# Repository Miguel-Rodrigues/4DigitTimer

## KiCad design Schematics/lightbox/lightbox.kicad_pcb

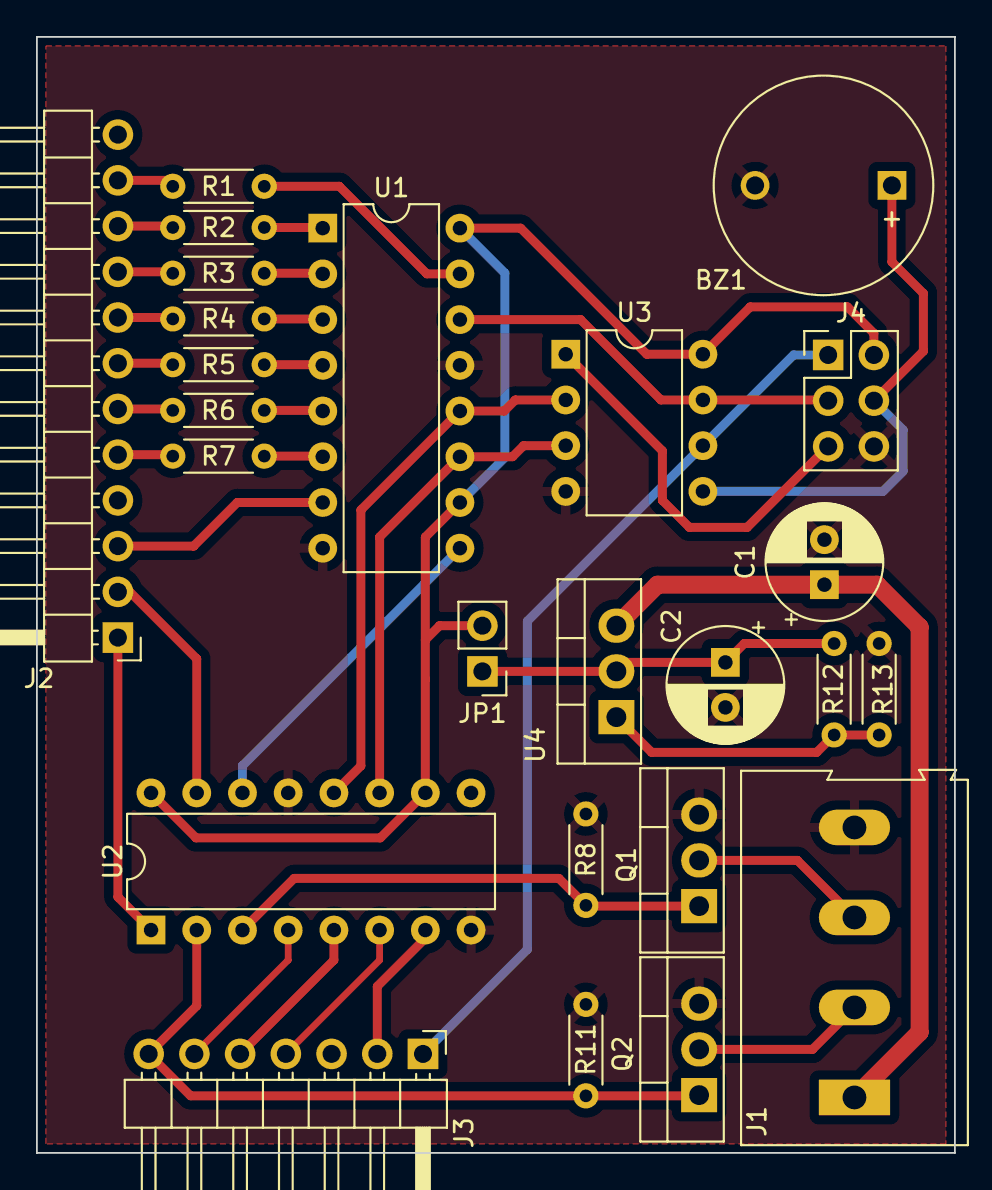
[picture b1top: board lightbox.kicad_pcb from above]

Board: 2 copper layers, 51.0 x 62.0 mm, 25 parts (0 on the bottom side), 37 nets.

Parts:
BZ1: Buzzer; MagneticBuzzer_ProSignal_ABI-010-RC
C1: 100nF; CP_Radial_D6.3mm_P2.50mm
C2: 1µF; CP_Radial_D6.3mm_P2.50mm
J1: Screw_Terminal_01x04; TerminalBlock_Altech_AK300-4_P5.00mm
J2: Conn_01x11_Pin; PinHeader_1x12_P2.54mm_Horizontal
J3: Conn_01x07_Pin; PinHeader_1x07_P2.54mm_Horizontal
J4: Conn_02x03_Odd_Even; PinHeader_2x03_P2.54mm_Vertical
JP1: Jumper_2_Bridged; PinHeader_1x02_P2.54mm_Vertical
Q1, Q2: IRF530; TO-220-3_Vertical
R1, R2, R3, R4, R5, R6, R7: 470R; R_Axial_DIN0204_L3.6mm_D1.6mm_P5.08mm_Horizontal
R8, R11: 10K; R_Axial_DIN0204_L3.6mm_D1.6mm_P5.08mm_Horizontal
R12: 100R; R_Axial_DIN0204_L3.6mm_D1.6mm_P5.08mm_Horizontal
R13: 220R; R_Axial_DIN0204_L3.6mm_D1.6mm_P5.08mm_Horizontal
U1: 74AHCT595; DIP-16_W7.62mm
U2: 74HC595; DIP-16_W7.62mm
U3: ATtiny85-20P; DIP-8_W7.62mm
U4: LM317_TO-220; TO-220-3_Vertical

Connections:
+12V: C1.1, J1.1, U4.3 (VI)
/A: J2.11, R1.2
/B: J2.10, R2.2
/Buzzer: BZ1.1 (-), J4.4, U3.5 (AREF/PB0)
/C: J2.9, R3.2
/Clk: U1.11 (SRCLK), U2.11 (SRCLK), U3.3 (XTAL2/PB4)
/D: J2.8, R4.2
/D_{1}: J3.1, J4.1, U3.6 (PB1)
/D_{2}: J4.3, U1.14 (SER), U3.7 (PB2)
/D_{3}: U1.12 (RCLK), U2.12 (RCLK), U3.2 (XTAL1/PB3)
/Digit1: J2.3, U1.7 (QH)
/Digit2: J2.2, U2.15 (QA)
/Digit3: J2.1, U2.1 (QB)
/E: J2.7, R5.2
/F: J2.6, R6.2
/G: J2.5, R7.2
/ISP_RST: J4.5, U3.1 (~RESET/PB5)
/QH': U1.9 (QH'), U2.14 (SER)
/REDLeds: Q1.1, R8.2, U2.3 (QD)
/RED_Led_Array: J1.3, Q1.2
/SW_Push_+: J3.4, U2.6 (QG)
/SW_Push_-: J3.6, U2.4 (QE)
/SW_Push_RESET: J3.5, U2.5 (QF)
/SW_Push_START: J3.2, U2.7 (QH)
/UVLeds: J3.7, Q2.1, R11.2, U2.2 (QC)
/UV_Led_Array: J1.2, Q2.2
GND: BZ1.2 (+), C1.2, C2.2, J1.4, J3.3, J4.6, Q1.3, Q2.3, R8.1, R11.1, R13.1, U1.8 (GND), U1.13 (~OE), U2.8 (GND), U2.13 (~OE), U3.4 (GND)
unnamed: C2.1, JP1.1 (A), R12.2, U4.2 (VO)
unnamed: R1.1, U1.15 (QA)
unnamed: R2.1, U1.1 (QB)
unnamed: R3.1, U1.2 (QC)
unnamed: R4.1, U1.3 (QD)
unnamed: R5.1, U1.4 (QE)
unnamed: R6.1, U1.5 (QF)
unnamed: R7.1, U1.6 (QG)
unnamed: R12.1, R13.2, U4.1 (ADJ)
VCC: J4.2, JP1.2 (B), U1.10 (~SRCLR), U1.16 (VCC), U2.10 (~SRCLR), U2.16 (VCC), U3.8 (VCC)

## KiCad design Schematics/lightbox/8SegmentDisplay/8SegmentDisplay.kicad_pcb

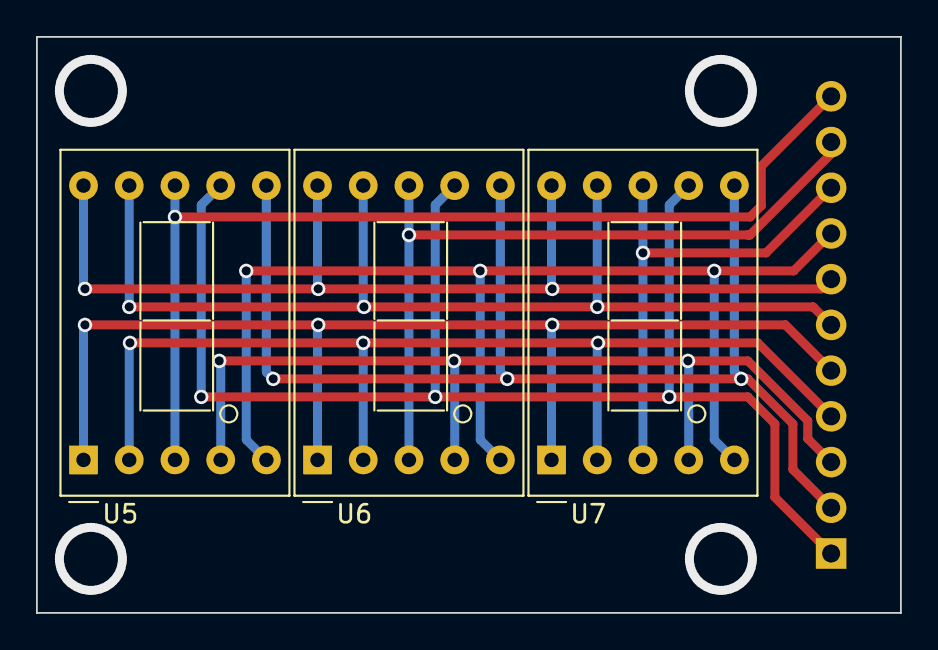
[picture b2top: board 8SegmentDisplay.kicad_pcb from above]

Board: 2 copper layers, 48.0 x 32.0 mm, 4 parts (1 on the bottom side), 11 nets.

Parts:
J4: Conn_01x11_Female; PinHeader_1x11_P2.54mm_Horizontal
U5, U6, U7: D148K; D1X8K

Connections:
/A: J4.1, U5.7 (A), U6.7 (A), U7.7 (A)
/B: J4.2, U5.6 (B), U6.6 (B), U7.6 (B)
/C: J4.3, U5.4 (C), U6.4 (C), U7.4 (C)
/D: J4.4, U5.2 (D), U6.2 (D), U7.2 (D)
/Digit1: J4.11, U5.3 (CC), U5.8 (CC)
/Digit2: J4.10, U6.3 (CC), U6.8 (CC)
/Digit3: J4.9, U7.3 (CC), U7.8 (CC)
/E: J4.5, U5.1 (E), U6.1 (E), U7.1 (E)
/F: J4.6, U5.9 (F), U6.9 (F), U7.9 (F)
/G: J4.7, U5.10 (G), U6.10 (G), U7.10 (G)
/H: J4.8, U5.5 (DP), U6.5 (DP), U7.5 (DP)

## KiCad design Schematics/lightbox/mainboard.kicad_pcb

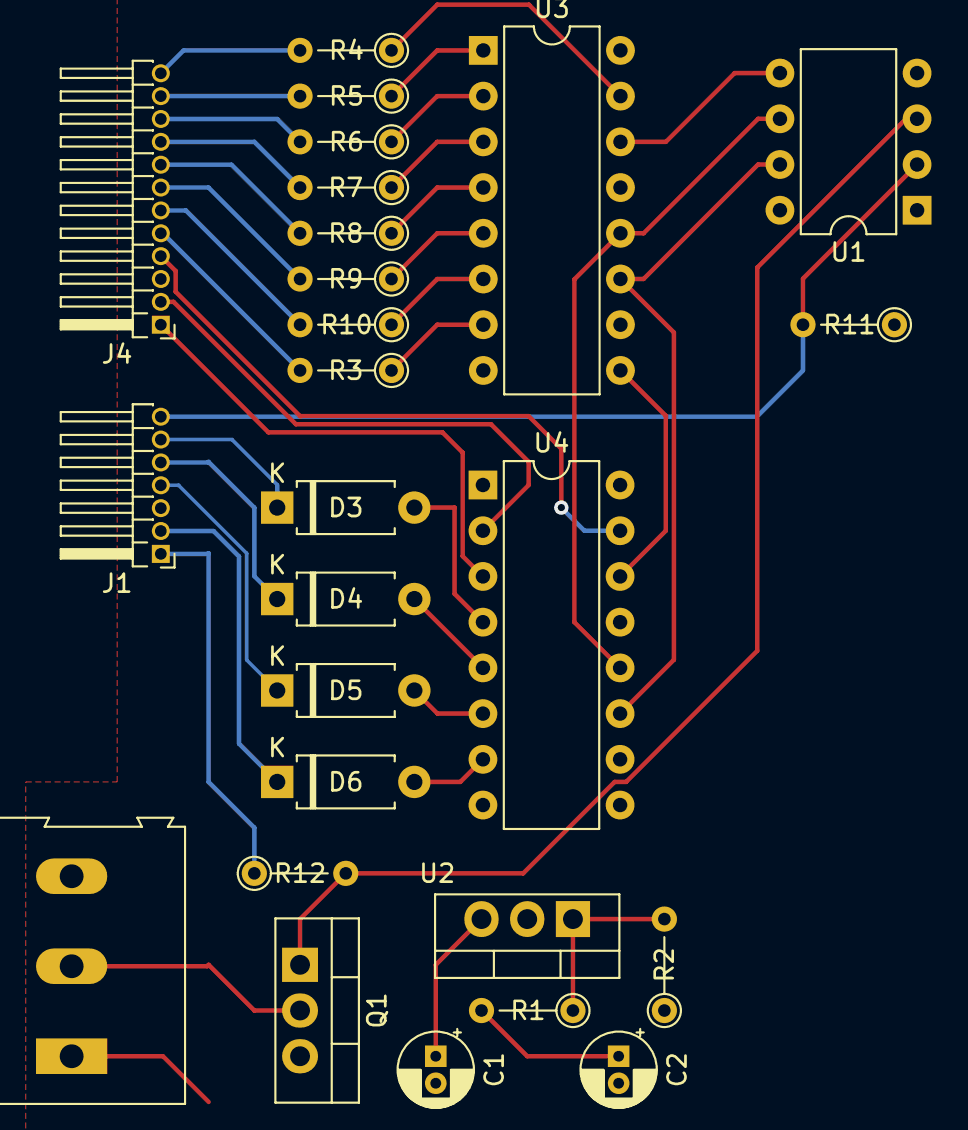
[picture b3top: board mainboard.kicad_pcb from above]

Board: 2 copper layers, 26 parts (0 on the bottom side), 40 nets.

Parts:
C1: 0.1µF; CP_Radial_D4.0mm_P1.50mm
C2: 10µF; CP_Radial_D4.0mm_P1.50mm
D3, D4, D5, D6: D; D_A-405_P7.62mm_Horizontal
J1: Conn_01x07_Female; PinHeader_1x07_P1.27mm_Horizontal
J2: Screw_Terminal_01x03; TerminalBlock_Altech_AK300-3_P5.00mm
J4: Conn_01x12_Female; PinHeader_1x12_P1.27mm_Horizontal
Q1: IRF740; TO-220-3_Vertical
R1, R11: 1K; R_Axial_DIN0204_L3.6mm_D1.6mm_P5.08mm_Vertical
R2: 1.5K; R_Axial_DIN0204_L3.6mm_D1.6mm_P5.08mm_Vertical
R3, R4, R5, R6, R7, R8, R9, R10, R12: 470R; R_Axial_DIN0204_L3.6mm_D1.6mm_P5.08mm_Vertical
U1: ATtiny85-20P; DIP-8_W7.62mm
U2: LM317_TO-220; TO-220-3_Vertical
U3: 74AHCT595; DIP-16_W7.62mm
U4: 74HC595; DIP-16_W7.62mm

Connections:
+3V3: C2.1, R1.2, U1.8 (VCC), U2.2 (VO), U3.10 (~SRCLR), U3.16 (VCC), U4.10 (~SRCLR), U4.16 (VCC)
+12V: C1.1, J2.1, U2.3 (VI)
/A: J4.12, R4.2
/B: J4.11, R5.2
/C: J4.10, R6.2
/Clk: U1.7 (PB2), U3.11 (SRCLK), U4.11 (SRCLK)
/D: J4.9, R7.2
/Data: U1.5 (AREF/PB0), U3.14 (SER)
/Digit1: J4.4, U4.15 (QA)
/Digit2: J4.3, U4.1 (QB)
/Digit3: J4.2, U4.2 (QC)
/Digit4: J4.1, U4.3 (QD)
/E: J4.8, R8.2
/F: J4.7, R9.2
/G: J4.6, R10.2
/H: J4.5, R3.2
/Keypad: J1.7, R11.2, U1.2 (XTAL1/PB3)
/Led: J1.1, R12.1
/Led_Array: J2.2, Q1.2 (D)
/Leds: Q1.1 (G), R12.2, U1.3 (XTAL2/PB4)
/QH': U3.9 (QH'), U4.14 (SER)
/Rclk: U1.6 (PB1), U3.12 (RCLK), U4.12 (RCLK)
/SW_Push_+: D5.1 (K), J1.4
/SW_Push_-: D3.1 (K), J1.6
/SW_Push_RESET: D4.1 (K), J1.5
/SW_Push_START: D6.1 (K), J1.2
GND: C1.2, C2.2, J1.3, J2.3, Q1.3 (S), R2.1, R11.1, U1.4 (GND), U3.8 (GND), U3.13 (~OE), U4.8 (GND), U4.13 (~OE)
unnamed: D3.2 (A), U4.4 (QE)
unnamed: D4.2 (A), U4.5 (QF)
unnamed: D5.2 (A), U4.6 (QG)
unnamed: D6.2 (A), U4.7 (QH)
unnamed: R1.1, R2.2, U2.1 (ADJ)
unnamed: R3.1, U3.7 (QH)
unnamed: R4.1, U3.15 (QA)
unnamed: R5.1, U3.1 (QB)
unnamed: R6.1, U3.2 (QC)
unnamed: R7.1, U3.3 (QD)
unnamed: R8.1, U3.4 (QE)
unnamed: R9.1, U3.5 (QF)
unnamed: R10.1, U3.6 (QG)

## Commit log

2022-09-08 Use main loop to flush and iterate buffers; Refactoring; Code cleanup;
2022-09-09 Fix digit sequence; Write "donE."
2022-10-25 Update Schematic and PCB layout
2022-10-25 Add Timer logic; Code cleanup; setup button events
2022-10-29 Fix timer countdown; setup leds;
2022-12-03 Fix Timer logic;
2022-12-03 Fix Timer blinking; Add blanks "---" for timeless mode;
2022-12-03 Add timeless mode
2022-12-04 Replace UV pin with buzzer; Remove dot pin and rearrange register for UV Pin;
2022-12-04 Update schematics for new buzzer
2022-12-04 Add buzzer tones
2022-12-04 Fix Leds register pins
2022-12-04 Separate system timer from countdown timer
2022-12-04 Configure pin layout for ATTiny85 and Arduino Uno
2022-12-04 remove unnecessary diodes
2022-12-04 Fix annotations
2022-12-04 Add Fuses for 8MHz on ATTiny
2022-12-04 Update schematics
2022-12-05 Fix buzzer, using single tone buzzer.
2022-12-05 Revert schematics
2022-12-09 Update PCB Layout; Update Regulator design
2022-12-09 Replace IRF740 by IRF530; Update PCB Layout; Plot PCB Layers
2022-12-09 Update PCB layout; Clear acid traps; Generate new layers
2023-05-28 Update lightbox design
2023-05-28 remove cache and temp files
